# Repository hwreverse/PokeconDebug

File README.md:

# PokeconDebug
Breakout &amp; Debug Boards for Vintage Pocket Computers (ポケコン) from Casio, Sharp,... and their Accessories<br>

- <a href="Casio/">Casio Debug Boards</a>

- <a href="Sharp/">Sharp Debug Boards</a>

I'll make some for TRS80 Model100 too, when I get to it

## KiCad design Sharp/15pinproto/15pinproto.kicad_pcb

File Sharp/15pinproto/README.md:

# Sharp 15pin Prototyping Board for Sharp PC-E500 / PC-1600

All resistors and LEDs are 0805<br>
The 15pin connector is a 1x15pin male 1.27mm(50mil) pitch connector

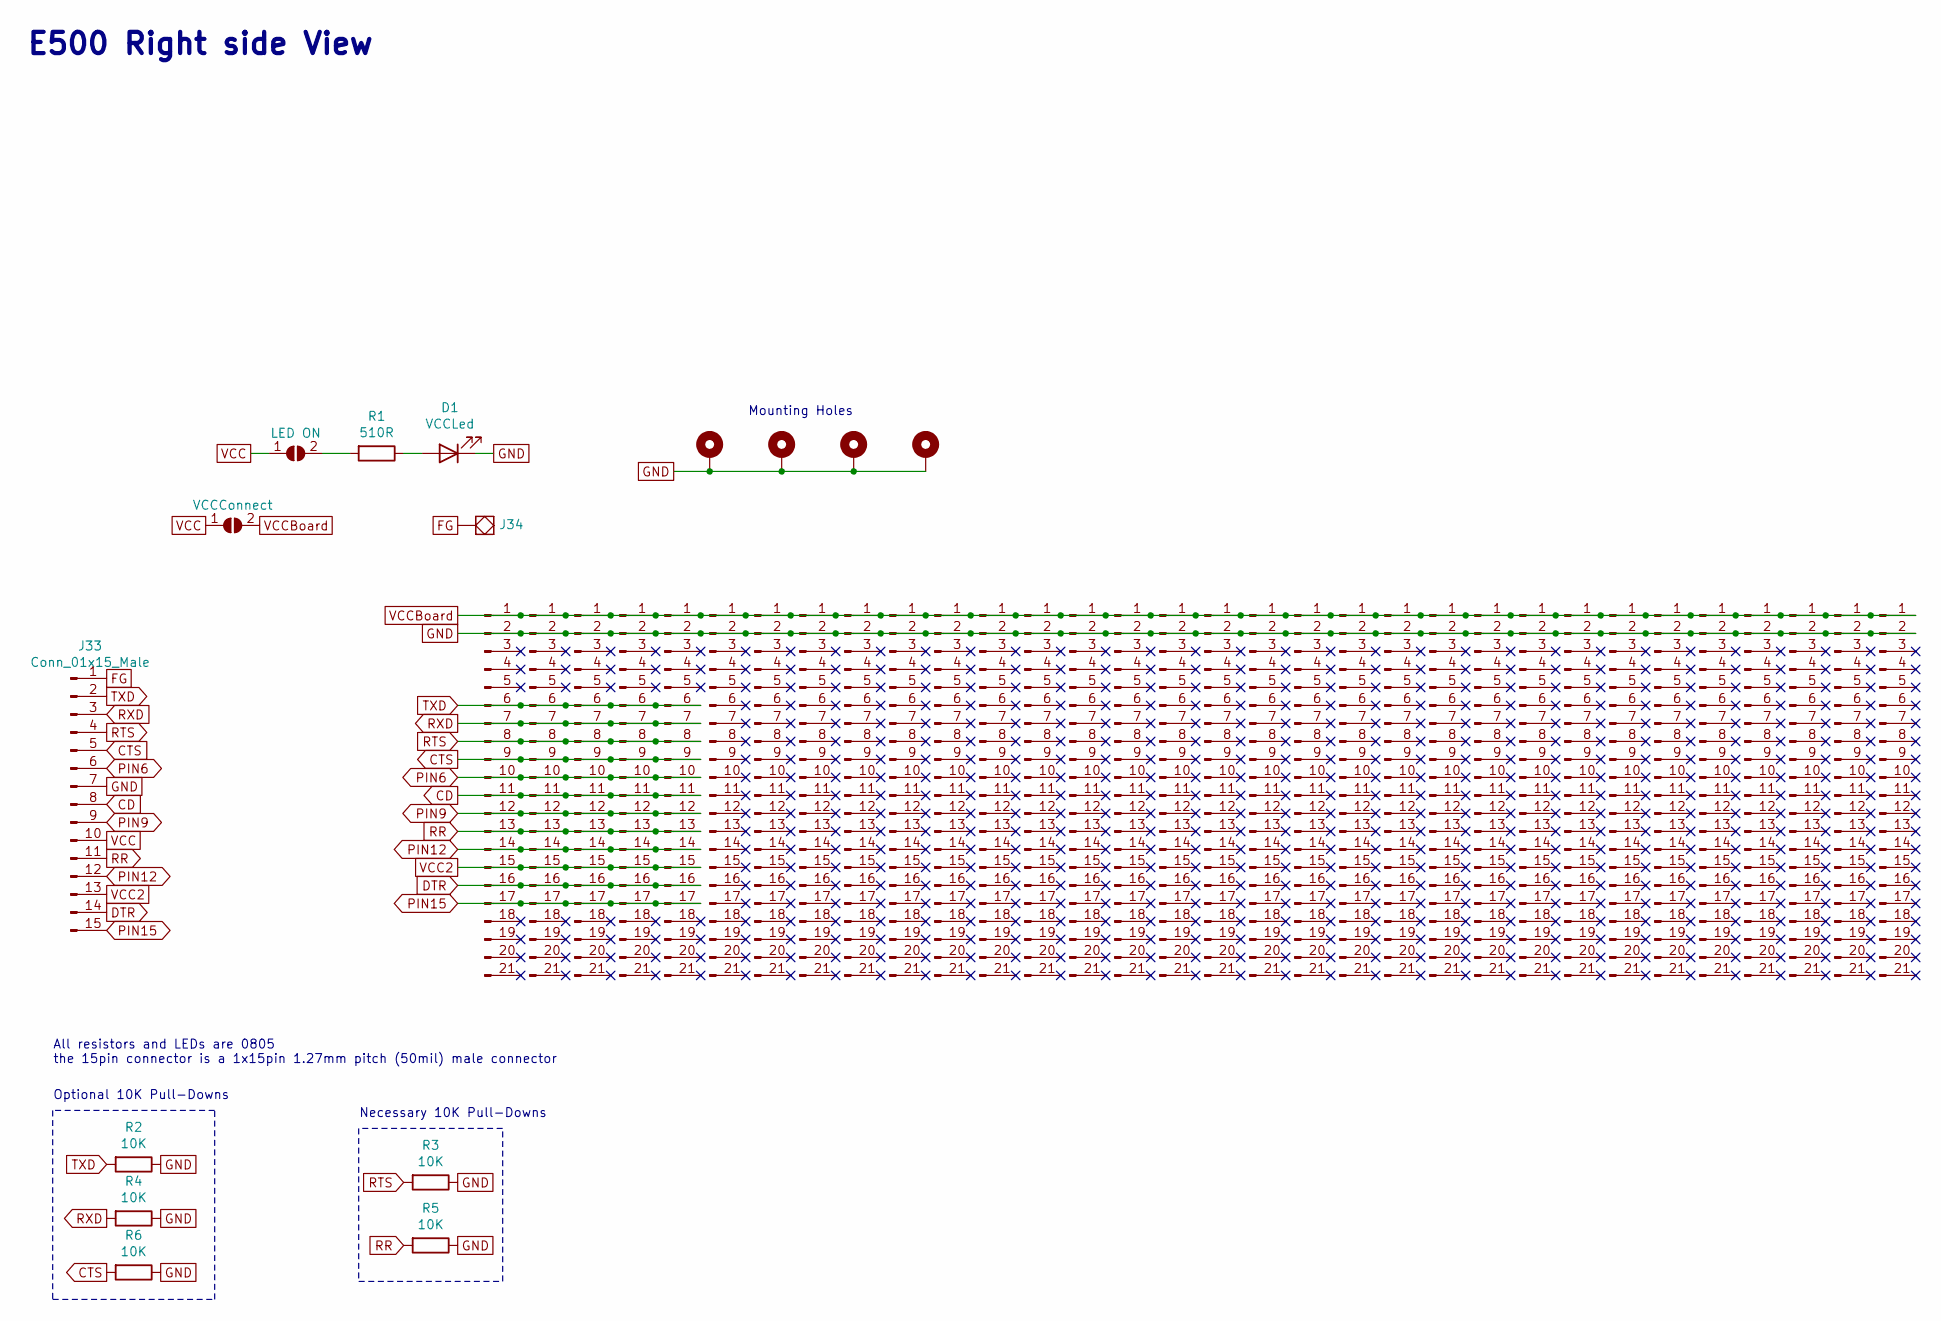
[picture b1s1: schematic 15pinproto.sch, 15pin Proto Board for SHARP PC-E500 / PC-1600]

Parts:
D1: VCCLed; LED_0805_2012Metric_Pad1.15x1.40mm_HandSolder
H1, H2, H3, H4: MountingHole_Pad; MountingHole_2.5mm_Pad
J1, J2, J3, J4, J5, J6, J7, J8, J9, J10, J11, J12, J13, J14, J15, J16, J17, J18, J19, J20, J21, J22, J23, J24, J25, J26, J27, J28, J29, J30, J31, J32: Conn_01x21_Male; PinHeader_1x21_P2.54mm_Vertical_nocrtyard+justholes
J33: Conn_01x15_Male; PinHeader_1x15_P1.27mm_Vertical
J34: SolidPad-Connector; SolidPad_4x4mm_2x2mmCore
JP1: LED ON; SolderJumper-2_P1.3mm_Open_RoundedPad1.0x1.5mm
JP2: VCCConnect; SolderJumper-2_P1.3mm_Open_RoundedPad1.0x1.5mm
R1: 510R; R_0805_2012Metric_Pad1.15x1.40mm_HandSolder
R2, R3, R4, R5, R6: 10K; R_0805_2012Metric_Pad1.15x1.40mm_HandSolder

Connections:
CD: J1.11, J2.11, J3.11, J4.11, J5.11, J33.8
CTS: J1.9, J2.9, J3.9, J4.9, J5.9, J33.5, R6.2
DTR: J1.16, J2.16, J3.16, J4.16, J5.16, J33.14
FG: J33.1, J34.~
GND: D1.1 (K), H1.1, H2.1, H3.1, H4.1, J1.2, J2.2, J3.2, J4.2, J5.2, J6.2, J7.2, J8.2, J9.2, J10.2, J11.2, J12.2, J13.2, J14.2, J15.2, J16.2, J17.2, J18.2, J19.2, J20.2, J21.2, J22.2, J23.2, J24.2, J25.2, J26.2, J27.2, J28.2, J29.2, J30.2, J31.2, J32.2, J33.7, R2.1, R3.1, R4.1, R5.1, R6.1
unnamed: D1.2 (A), R1.1
unnamed: JP1.2 (B), R1.2
PIN6: J1.10, J2.10, J3.10, J4.10, J5.10, J33.6
PIN9: J1.12, J2.12, J3.12, J4.12, J5.12, J33.9
PIN12: J1.14, J2.14, J3.14, J4.14, J5.14, J33.12
PIN15: J1.17, J2.17, J3.17, J4.17, J5.17, J33.15
RR: J1.13, J2.13, J3.13, J4.13, J5.13, J33.11, R5.2
RTS: J1.8, J2.8, J3.8, J4.8, J5.8, J33.4, R3.2
RXD: J1.7, J2.7, J3.7, J4.7, J5.7, J33.3, R4.2
TXD: J1.6, J2.6, J3.6, J4.6, J5.6, J33.2, R2.2
VCC: J33.10, JP1.1 (A), JP2.1 (A)
VCC2: J1.15, J2.15, J3.15, J4.15, J5.15, J33.13
VCCBoard: J1.1, J2.1, J3.1, J4.1, J5.1, J6.1, J7.1, J8.1, J9.1, J10.1, J11.1, J12.1, J13.1, J14.1, J15.1, J16.1, J17.1, J18.1, J19.1, J20.1, J21.1, J22.1, J23.1, J24.1, J25.1, J26.1, J27.1, J28.1, J29.1, J30.1, J31.1, J32.1, JP2.2 (B)

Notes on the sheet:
E500 Right side View
Optional 10K Pull-Downs
Necessary 10K Pull-Downs
Mounting Holes
All resistors and LEDs are 0805 the 15pin connector is a 1x15pin 1.27mm pitch (50mil) male connector

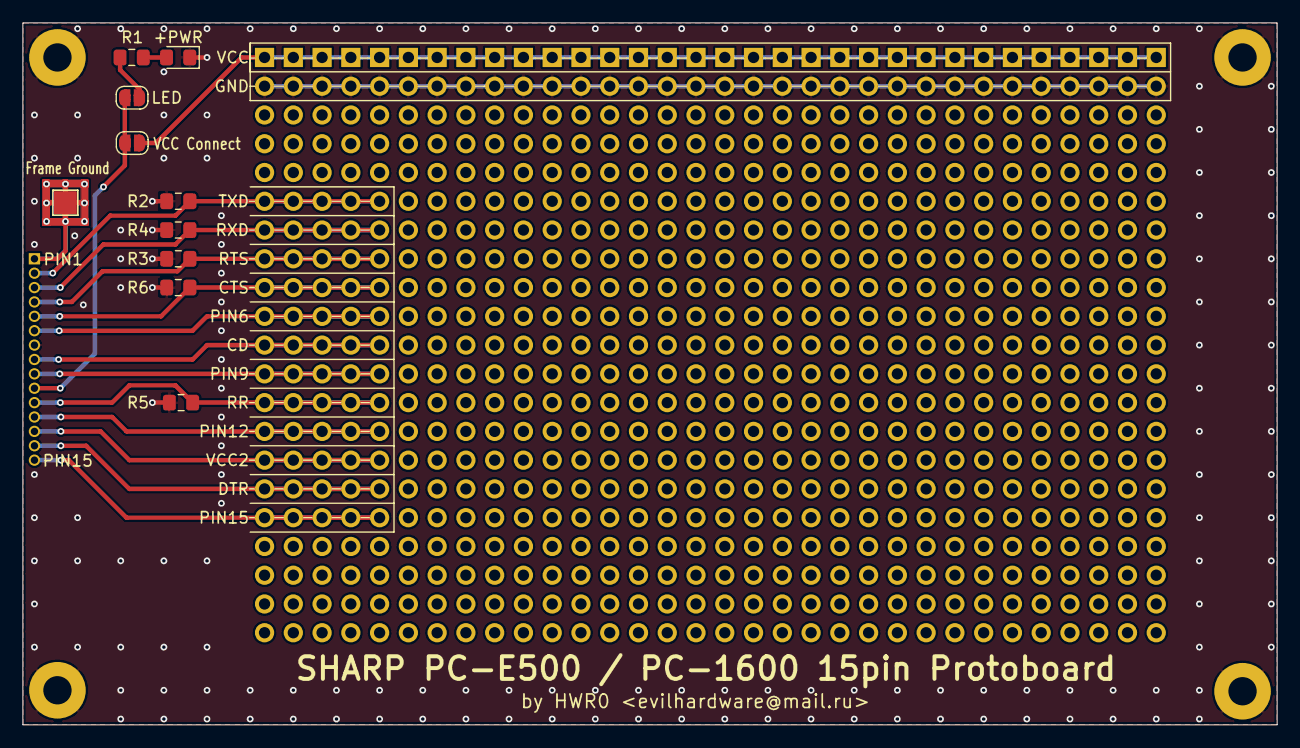
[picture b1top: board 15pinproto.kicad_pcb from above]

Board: 2 copper layers, 110.7 x 62.0 mm, 47 parts (0 on the bottom side), 18 nets.

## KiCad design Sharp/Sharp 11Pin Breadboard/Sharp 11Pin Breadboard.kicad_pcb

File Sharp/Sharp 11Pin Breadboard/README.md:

# Sharp 11pin Prototyping Board for Sharp PC-G850*,...

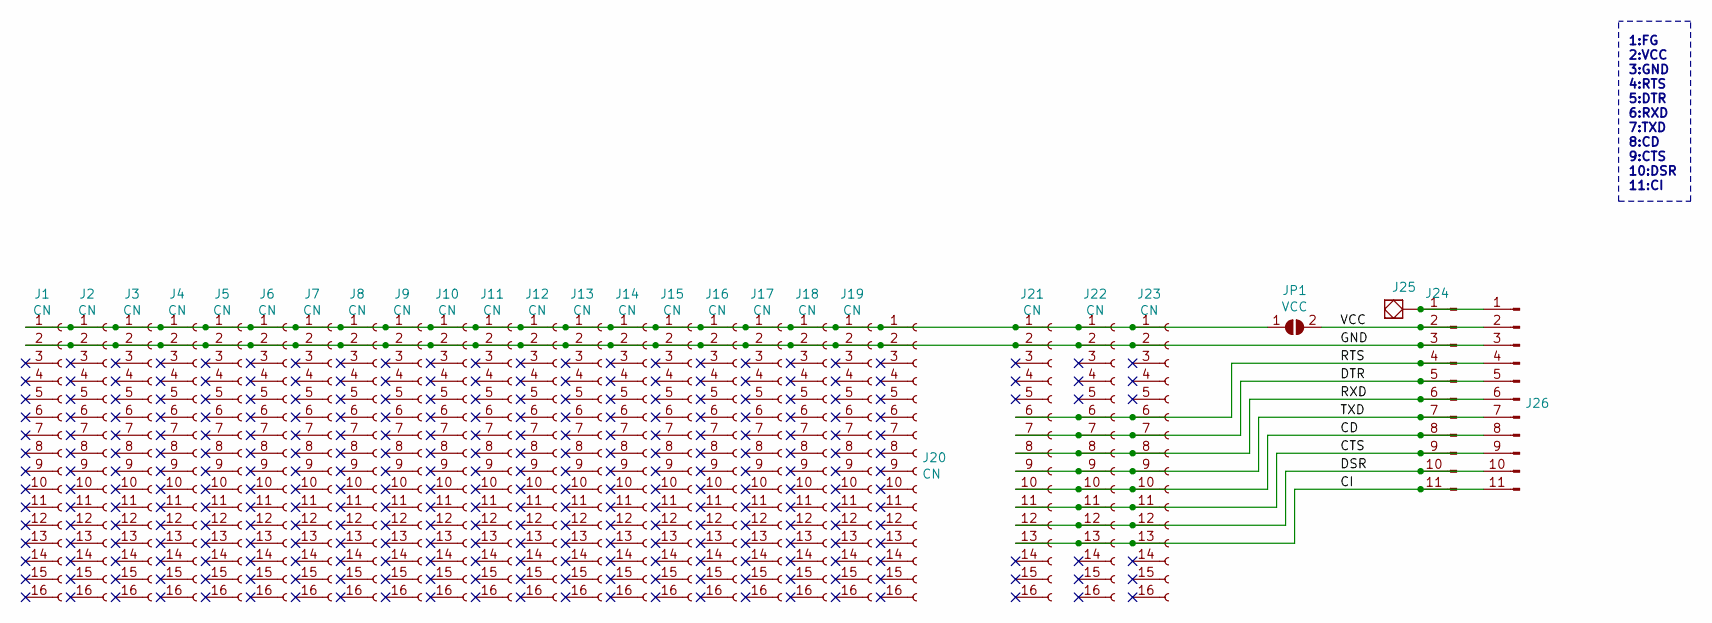
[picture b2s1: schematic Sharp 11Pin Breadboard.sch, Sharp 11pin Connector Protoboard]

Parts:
J1, J2, J3, J4, J5, J6, J7, J8, J9, J10, J11, J12, J13, J14, J15, J16, J17, J18, J19, J20, J21, J22, J23: CN; Breadboard_2.54mm_1x16
J24: CNDup; BreadBoard_2.54mm_1x11
J25: SolidPad-Connector; SolidPad_octa_2.2_1.4mmCore
J26: Conn_01x11_Male; PinHeader_1x11_P2.54mm_Horizontal
JP1: VCC; SolderJumper-2_P1.3mm_Open_RoundedPad1.0x1.5mm

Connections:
/CD: J21.10, J22.10, J23.10, J24.8, J26.8
/CI: J21.13, J22.13, J23.13, J24.11, J26.11
/CTS: J21.11, J22.11, J23.11, J24.9, J26.9
/DSR: J21.12, J22.12, J23.12, J24.10, J26.10
/DTR: J21.7, J22.7, J23.7, J24.5, J26.5
/GND: J1.2, J2.2, J3.2, J4.2, J5.2, J6.2, J7.2, J8.2, J9.2, J10.2, J11.2, J12.2, J13.2, J14.2, J15.2, J16.2, J17.2, J18.2, J19.2, J20.2, J21.2, J22.2, J23.2, J24.3, J26.3
/RTS: J21.6, J22.6, J23.6, J24.4, J26.4
/RXD: J21.8, J22.8, J23.8, J24.6, J26.6
/TXD: J21.9, J22.9, J23.9, J24.7, J26.7
/VCC: J24.2, J26.2, JP1.2 (B)
unnamed: J1.1, J2.1, J3.1, J4.1, J5.1, J6.1, J7.1, J8.1, J9.1, J10.1, J11.1, J12.1, J13.1, J14.1, J15.1, J16.1, J17.1, J18.1, J19.1, J20.1, J21.1, J22.1, J23.1, JP1.1 (A)
unnamed: J24.1, J25.~, J26.1

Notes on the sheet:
1:FG 2:VCC 3:GND 4:RTS 5:DTR 6:RXD 7:TXD 8:CD 9:CTS 10:DSR 11:CI

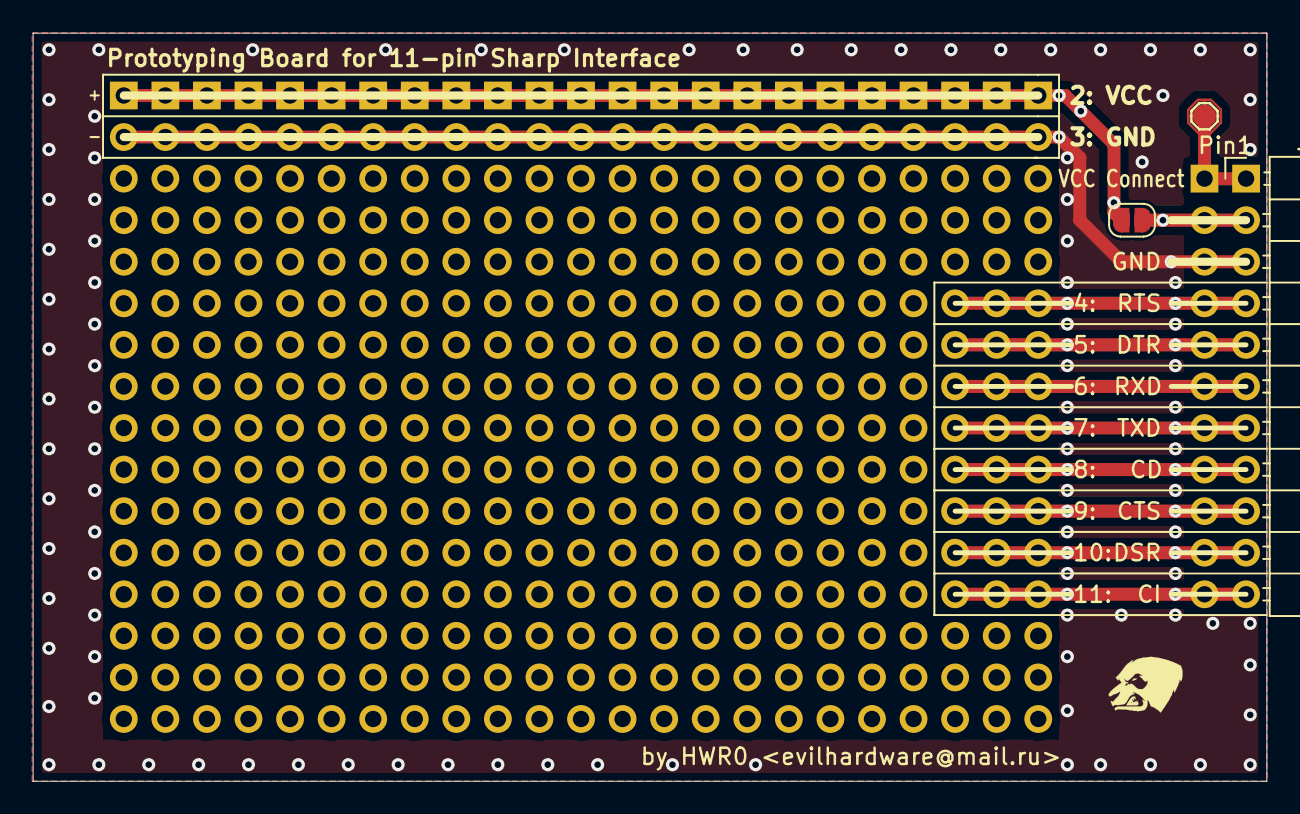
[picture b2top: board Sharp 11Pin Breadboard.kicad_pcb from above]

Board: 2 copper layers, 75.4 x 45.7 mm, 27 parts (0 on the bottom side), 12 nets.

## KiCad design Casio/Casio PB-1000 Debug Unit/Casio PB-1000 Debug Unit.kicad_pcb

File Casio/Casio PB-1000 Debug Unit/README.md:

# Casio PB-1000/2000C/AI-1000 System Bus Debug Board

SALEAE Logic Analyzer friendly (Ground pins with every Bus Pin, Groups of 2x4)

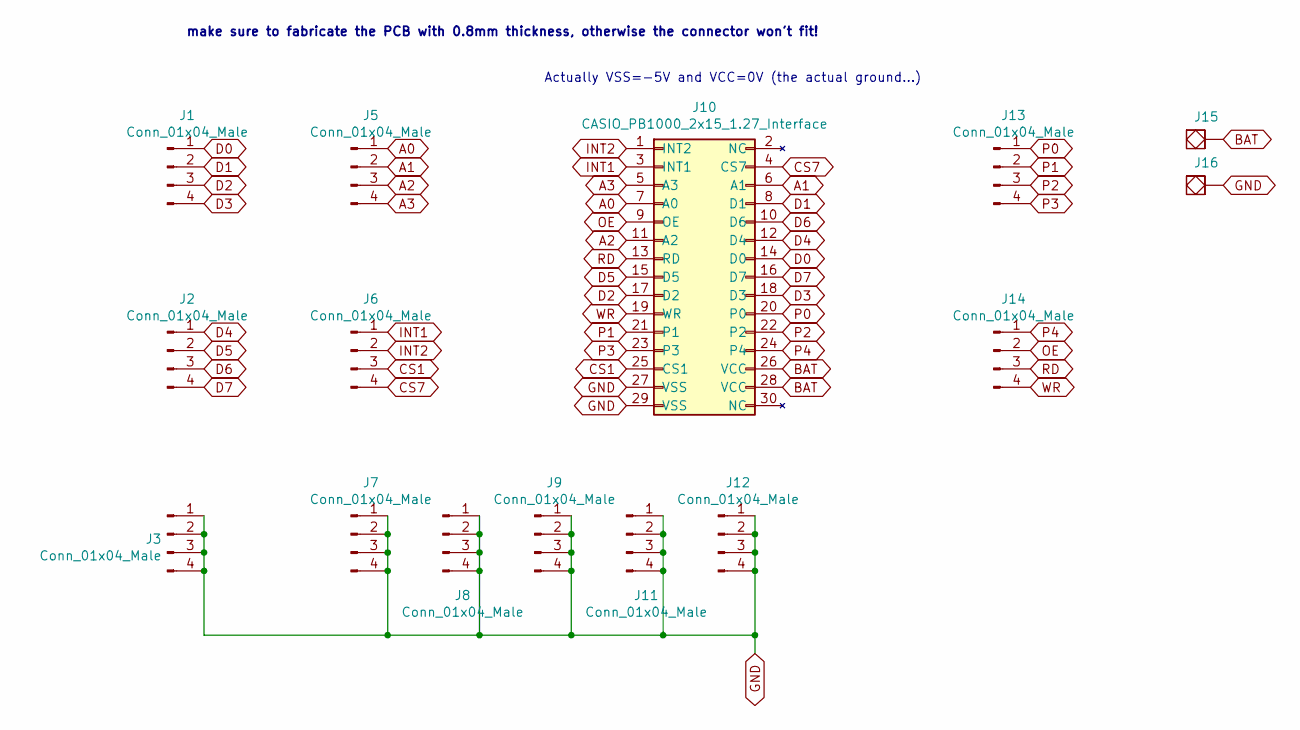
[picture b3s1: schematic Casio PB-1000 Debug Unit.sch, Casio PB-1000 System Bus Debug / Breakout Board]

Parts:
J1, J2, J3, J5, J6, J7, J8, J9, J11, J12, J13, J14: Conn_01x04_Male; PinHeader_1x04_P2.54mm_Vertical_nosilk
J10: CASIO_PB1000_2x15_1.27_Interface; Connector_Casio_2x15_1.27_SYSBUS
J15, J16: SolidPad-Connector; SolidPad_4x4mm_2x2mmCore

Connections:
A0: J5.1, J10.7 (A0)
A1: J5.2, J10.6 (A1)
A2: J5.3, J10.11 (A2)
A3: J5.4, J10.5 (A3)
BAT: J10.26 (VCC), J10.28 (VCC), J15.~
CS1: J6.3, J10.25 (CS1)
CS7: J6.4, J10.4 (CS7)
D0: J1.1, J10.14 (D0)
D1: J1.2, J10.8 (D1)
D2: J1.3, J10.17 (D2)
D3: J1.4, J10.18 (D3)
D4: J2.1, J10.12 (D4)
D5: J2.2, J10.15 (D5)
D6: J2.3, J10.10 (D6)
D7: J2.4, J10.16 (D7)
GND: J3.1, J3.2, J3.3, J3.4, J7.1, J7.2, J7.3, J7.4, J8.1, J8.2, J8.3, J8.4, J9.1, J9.2, J9.3, J9.4, J10.27 (VSS), J10.29 (VSS), J11.1, J11.2, J11.3, J11.4, J12.1, J12.2, J12.3, J12.4, J16.~
INT1: J6.1, J10.3 (INT1)
INT2: J6.2, J10.1 (INT2)
OE: J10.9 (OE), J14.2
P0: J10.20 (P0), J13.1
P1: J10.21 (P1), J13.2
P2: J10.22 (P2), J13.3
P3: J10.23 (P3), J13.4
P4: J10.24 (P4), J14.1
RD: J10.13 (RD), J14.3
WR: J10.19 (WR), J14.4

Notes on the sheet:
Actually VSS=-5V and VCC=0V (the actual ground...)
make sure to fabricate the PCB with 0.8mm thickness, otherwise the connector won't fit!

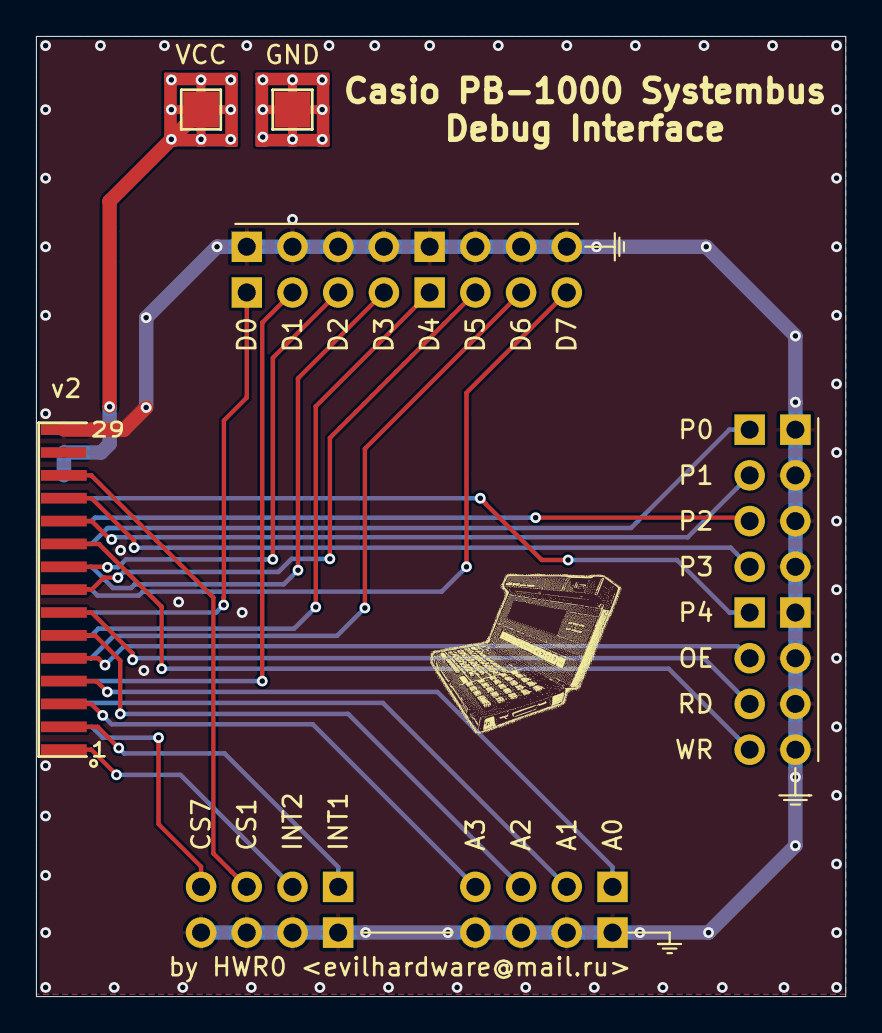
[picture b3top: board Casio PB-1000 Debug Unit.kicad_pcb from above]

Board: 2 copper layers, 45.0 x 53.3 mm, 15 parts (0 on the bottom side), 26 nets.

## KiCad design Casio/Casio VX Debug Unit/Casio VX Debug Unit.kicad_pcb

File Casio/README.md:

# Casio Debug & Proto Boards

- <a href="Casio%20PB-1000%20Debug%20Unit/">Casio PB-1000 Debug Board</a>

- <a href="Casio%20VX%20Debug%20Unit/">Casio VX-* Debug Board</a>

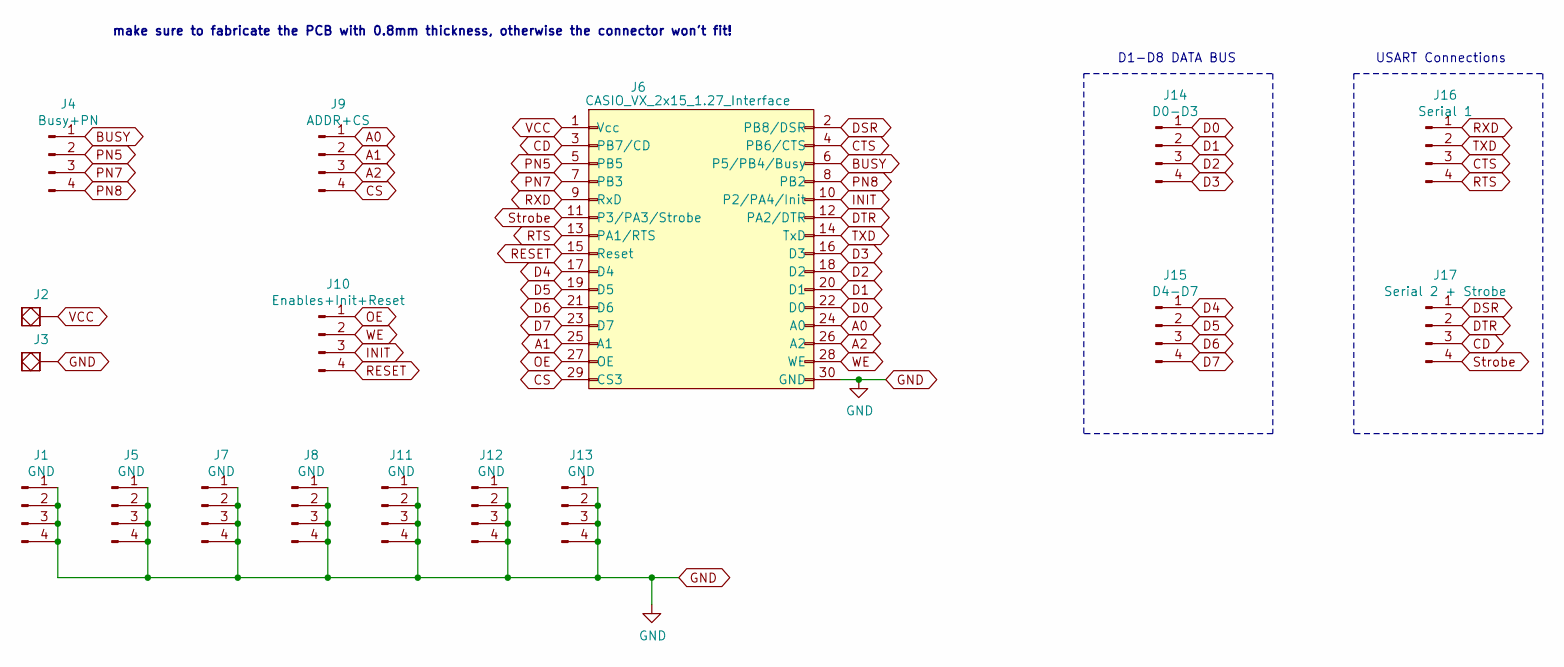
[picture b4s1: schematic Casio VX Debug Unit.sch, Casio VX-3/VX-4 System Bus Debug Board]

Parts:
J1, J5, J7, J8, J11, J12, J13: GND; PinHeader_1x04_P2.54mm_Vertical
J2, J3: SolidPad-Connector; SolidPad_4x4mm_2x2mmCore
J4: Busy+PN; PinHeader_1x04_P2.54mm_Vertical
J6: CASIO_VX_2x15_1.27_Interface; Connector_Casio_2x15_1.27_SYSBUS
J9: ADDR+CS; PinHeader_1x04_P2.54mm_Vertical
J10: Enables+Init+Reset; PinHeader_1x04_P2.54mm_Vertical
J14: D0-D3; PinHeader_1x04_P2.54mm_Vertical
J15: D4-D7; PinHeader_1x04_P2.54mm_Vertical
J16: Serial 1; PinHeader_1x04_P2.54mm_Vertical
J17: Serial 2 + Strobe; PinHeader_1x04_P2.54mm_Vertical

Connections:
A0: J6.24 (A0), J9.1
A1: J6.25 (A1), J9.2
A2: J6.26 (A2), J9.3
BUSY: J4.1, J6.6 (P5/PB4/Busy)
CD: J6.3 (PB7/CD), J17.3
CS: J6.29 (CS3), J9.4
CTS: J6.4 (PB6/CTS), J16.3
D0: J6.22 (D0), J14.1
D1: J6.20 (D1), J14.2
D2: J6.18 (D2), J14.3
D3: J6.16 (D3), J14.4
D4: J6.17 (D4), J15.1
D5: J6.19 (D5), J15.2
D6: J6.21 (D6), J15.3
D7: J6.23 (D7), J15.4
DSR: J6.2 (PB8/DSR), J17.1
DTR: J6.12 (PA2/DTR), J17.2
GND: J1.1, J1.2, J1.3, J1.4, J3.~, J5.1, J5.2, J5.3, J5.4, J6.30 (GND), J7.1, J7.2, J7.3, J7.4, J8.1, J8.2, J8.3, J8.4, J11.1, J11.2, J11.3, J11.4, J12.1, J12.2, J12.3, J12.4, J13.1, J13.2, J13.3, J13.4
INIT: J6.10 (P2/PA4/Init), J10.3
OE: J6.27 (OE), J10.1
PN5: J4.2, J6.5 (PB5)
PN7: J4.3, J6.7 (PB3)
PN8: J4.4, J6.8 (PB2)
RESET: J6.15 (Reset), J10.4
RTS: J6.13 (PA1/RTS), J16.4
RXD: J6.9 (RxD), J16.1
Strobe: J6.11 (P3/PA3/Strobe), J17.4
TXD: J6.14 (TxD), J16.2
VCC: J2.~, J6.1 (Vcc)
WE: J6.28 (WE), J10.2

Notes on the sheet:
D1-D8 DATA BUS
USART Connections
make sure to fabricate the PCB with 0.8mm thickness, otherwise the connector won't fit!

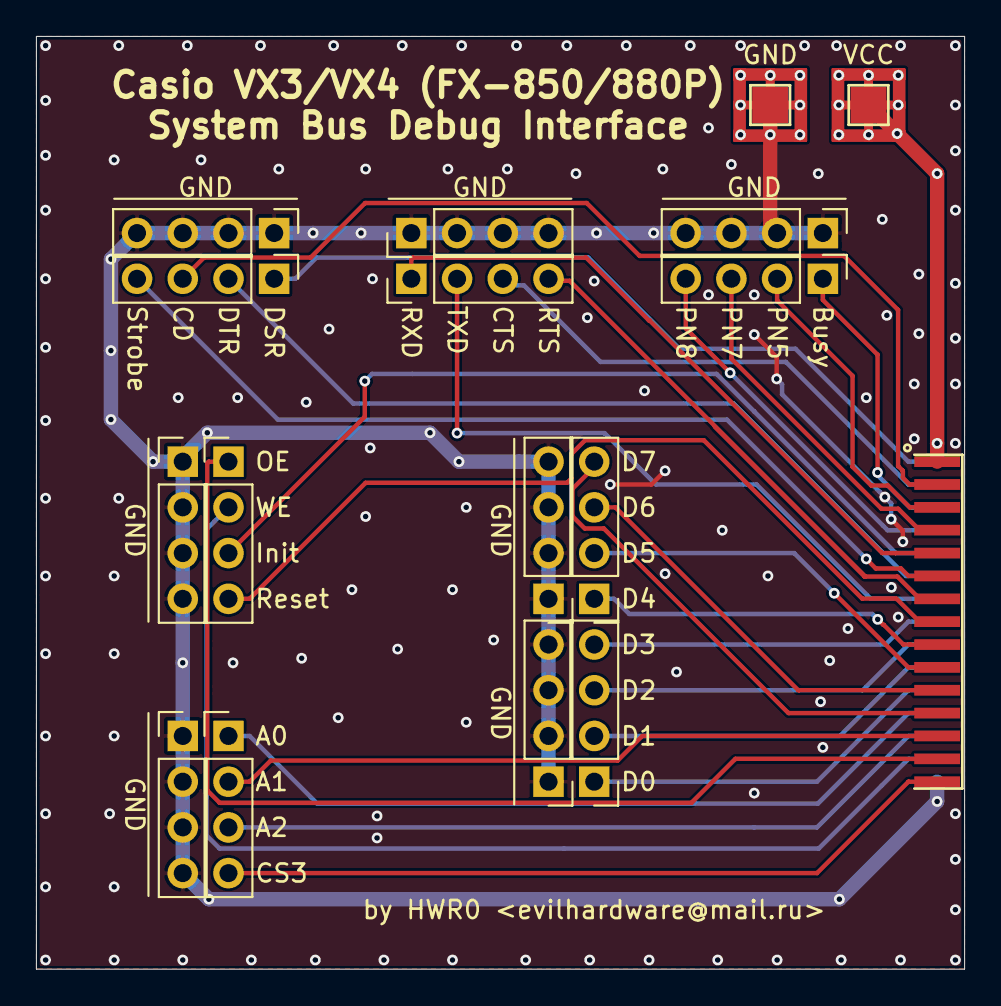
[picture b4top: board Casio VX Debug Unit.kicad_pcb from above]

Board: 2 copper layers, 51.6 x 51.8 mm, 17 parts (0 on the bottom side), 30 nets.

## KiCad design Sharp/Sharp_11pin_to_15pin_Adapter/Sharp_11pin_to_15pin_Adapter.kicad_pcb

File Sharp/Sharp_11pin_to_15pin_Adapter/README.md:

# Sharp 11pin to 15pin Adapter for Sharp PC-G850*, E500,...

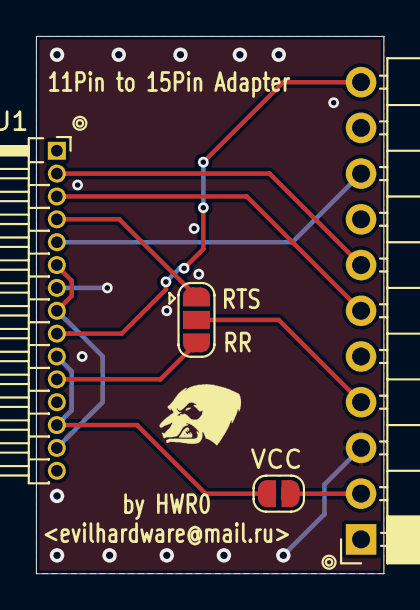
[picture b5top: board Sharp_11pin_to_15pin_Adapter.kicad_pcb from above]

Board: 2 copper layers, 19.3 x 29.8 mm, 4 parts (0 on the bottom side), 11 nets.

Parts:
J1: 15pin; PinHeader_1x15_P1.27mm_Horizontal_mirror
J2: 11pin; PinSocket_1x11_P2.54mm_Horizontal-mirror
JP1: E500/1600 Mode; SolderJumper-3_P1.3mm_Open_RoundedPad1.0x1.5mm
JP2: VCC Connect; SolderJumper-2_P1.3mm_Open_RoundedPad1.0x1.5mm

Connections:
/CI: J1.9, J2.11
/CTS: J1.5, J2.9
/GND: J1.7, J2.3
/RR15: J1.11, JP1.3
/RTS: J2.4, JP1.2
/RTS15: J1.4, JP1.1
/RXD: J1.3, J2.6
/Short15: J1.6, J1.8, J1.14
/TXD: J1.2, J2.7
/VCC15: J1.10, J1.13, JP2.1
unnamed: J2.2, JP2.2

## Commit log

2020-01-25 Initial Upload
2020-01-25 files removed
2020-08-25 added 15pin Protoboard
